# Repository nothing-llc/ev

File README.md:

# nothing-llc/ev

A place for Evan's msr-20-related files.

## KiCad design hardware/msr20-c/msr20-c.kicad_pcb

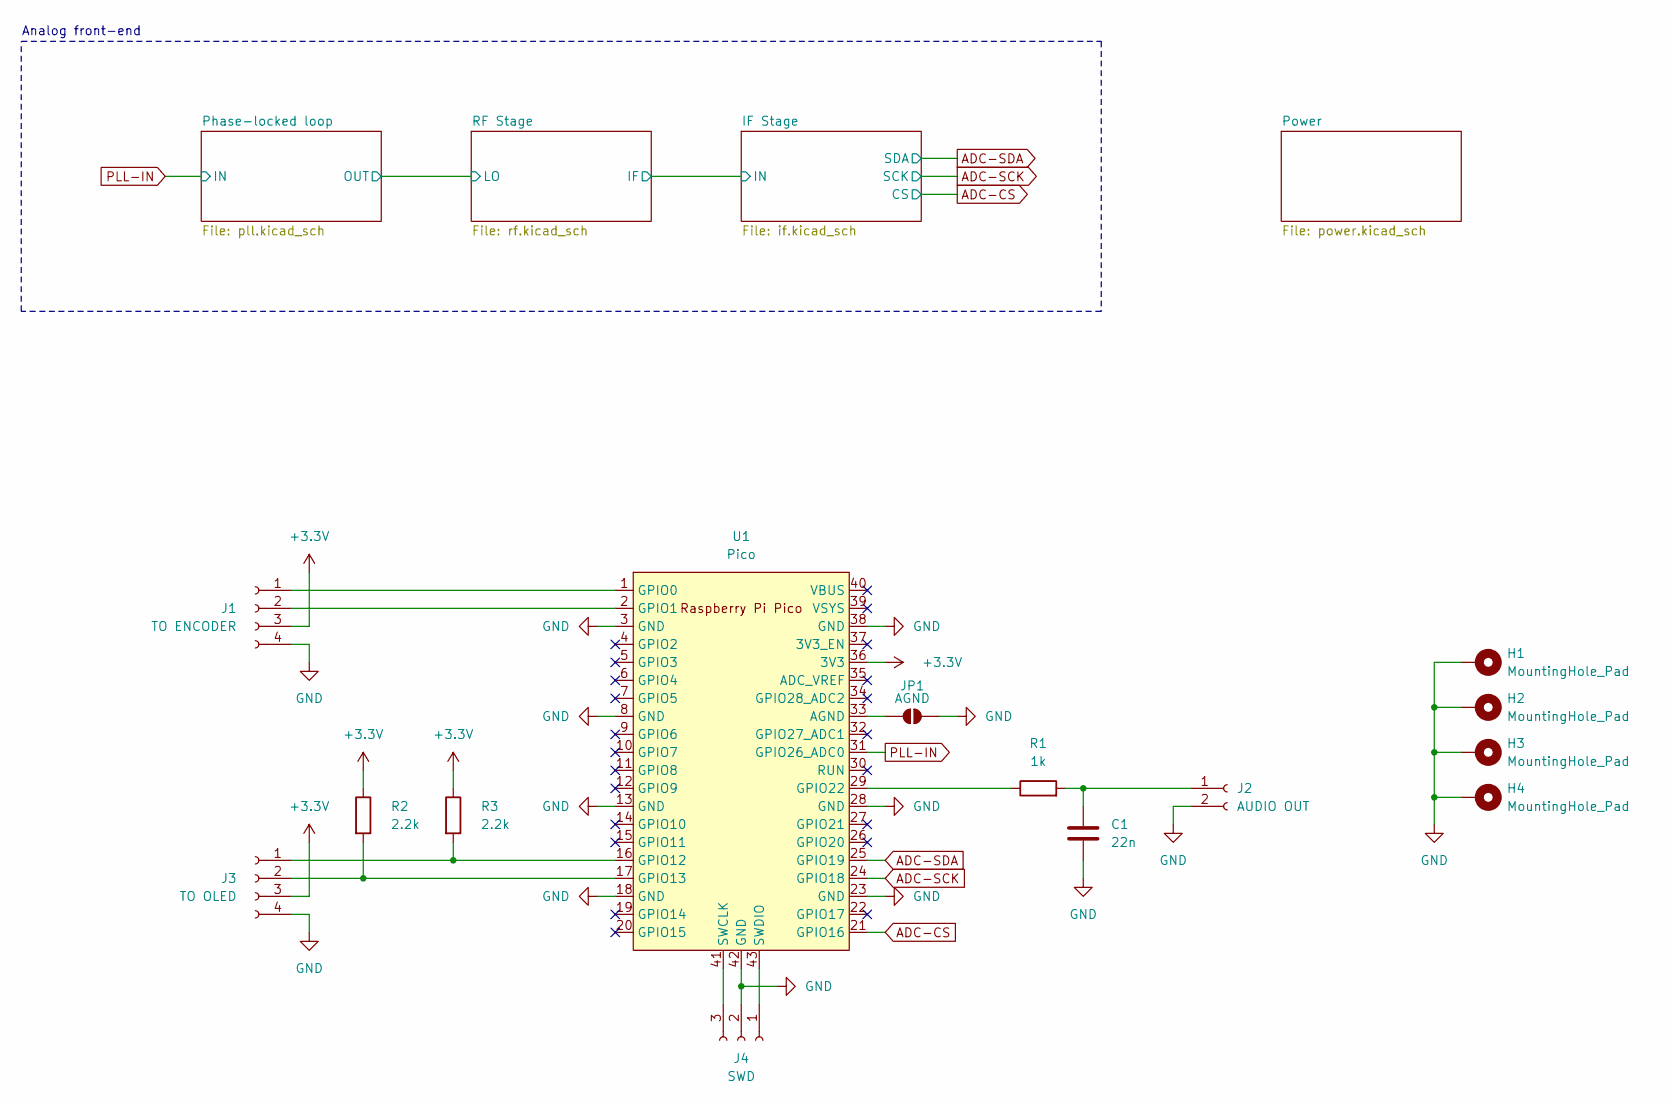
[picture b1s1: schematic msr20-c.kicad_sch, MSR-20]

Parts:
C1: 22n; C_0805_2012Metric
H1, H2, H3, H4: MountingHole_Pad; MountingHole_3.2mm_M3_DIN965_Pad_TopBottom
J1: TO ENCODER; PinHeader_1x04_P2.54mm_Vertical
J2: AUDIO OUT; PinHeader_1x02_P2.54mm_Vertical
J3: TO OLED; PinHeader_1x04_P2.54mm_Vertical
J4: SWD; PinHeader_1x03_P2.54mm_Vertical
JP1: AGND; SolderJumper-2_P1.3mm_Bridged_Pad1.0x1.5mm
R1: 1k; R_0805_2012Metric
R2, R3: 2.2k; R_0805_2012Metric
U1: Pico; RPi_Pico_SMD_TH

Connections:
+3.3V: J1.3, J3.3, R2.1, R3.1, U1.36 (3V3); also elsewhere on the board
ADC-CS: U1.21 (GPIO16); also elsewhere on the board
ADC-SCK: U1.24 (GPIO18); also elsewhere on the board
ADC-SDA: U1.25 (GPIO19); also elsewhere on the board
GND: C1.2, H1.1, H2.1, H3.1, H4.1, J1.4, J2.2, J3.4, J4.2, JP1.2 (B), U1.3 (GND), U1.8 (GND), U1.13 (GND), U1.18 (GND), U1.23 (GND), U1.28 (GND), U1.38 (GND), U1.42 (GND); also elsewhere on the board
unnamed: J1.1, U1.1 (GPIO0)
unnamed: J1.2, U1.2 (GPIO1)
unnamed: C1.1, J2.1, R1.2
unnamed: J3.1, R3.2, U1.16 (GPIO12)
unnamed: J3.2, R2.2, U1.17 (GPIO13)
unnamed: J4.1, U1.43 (SWDIO)
unnamed: J4.3, U1.41 (SWCLK)
unnamed: JP1.1 (A), U1.33 (AGND)
unnamed: R1.1, U1.29 (GPIO22)
PLL-IN: U1.31 (GPIO26_ADC0); also elsewhere on the board

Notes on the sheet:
Analog front-end

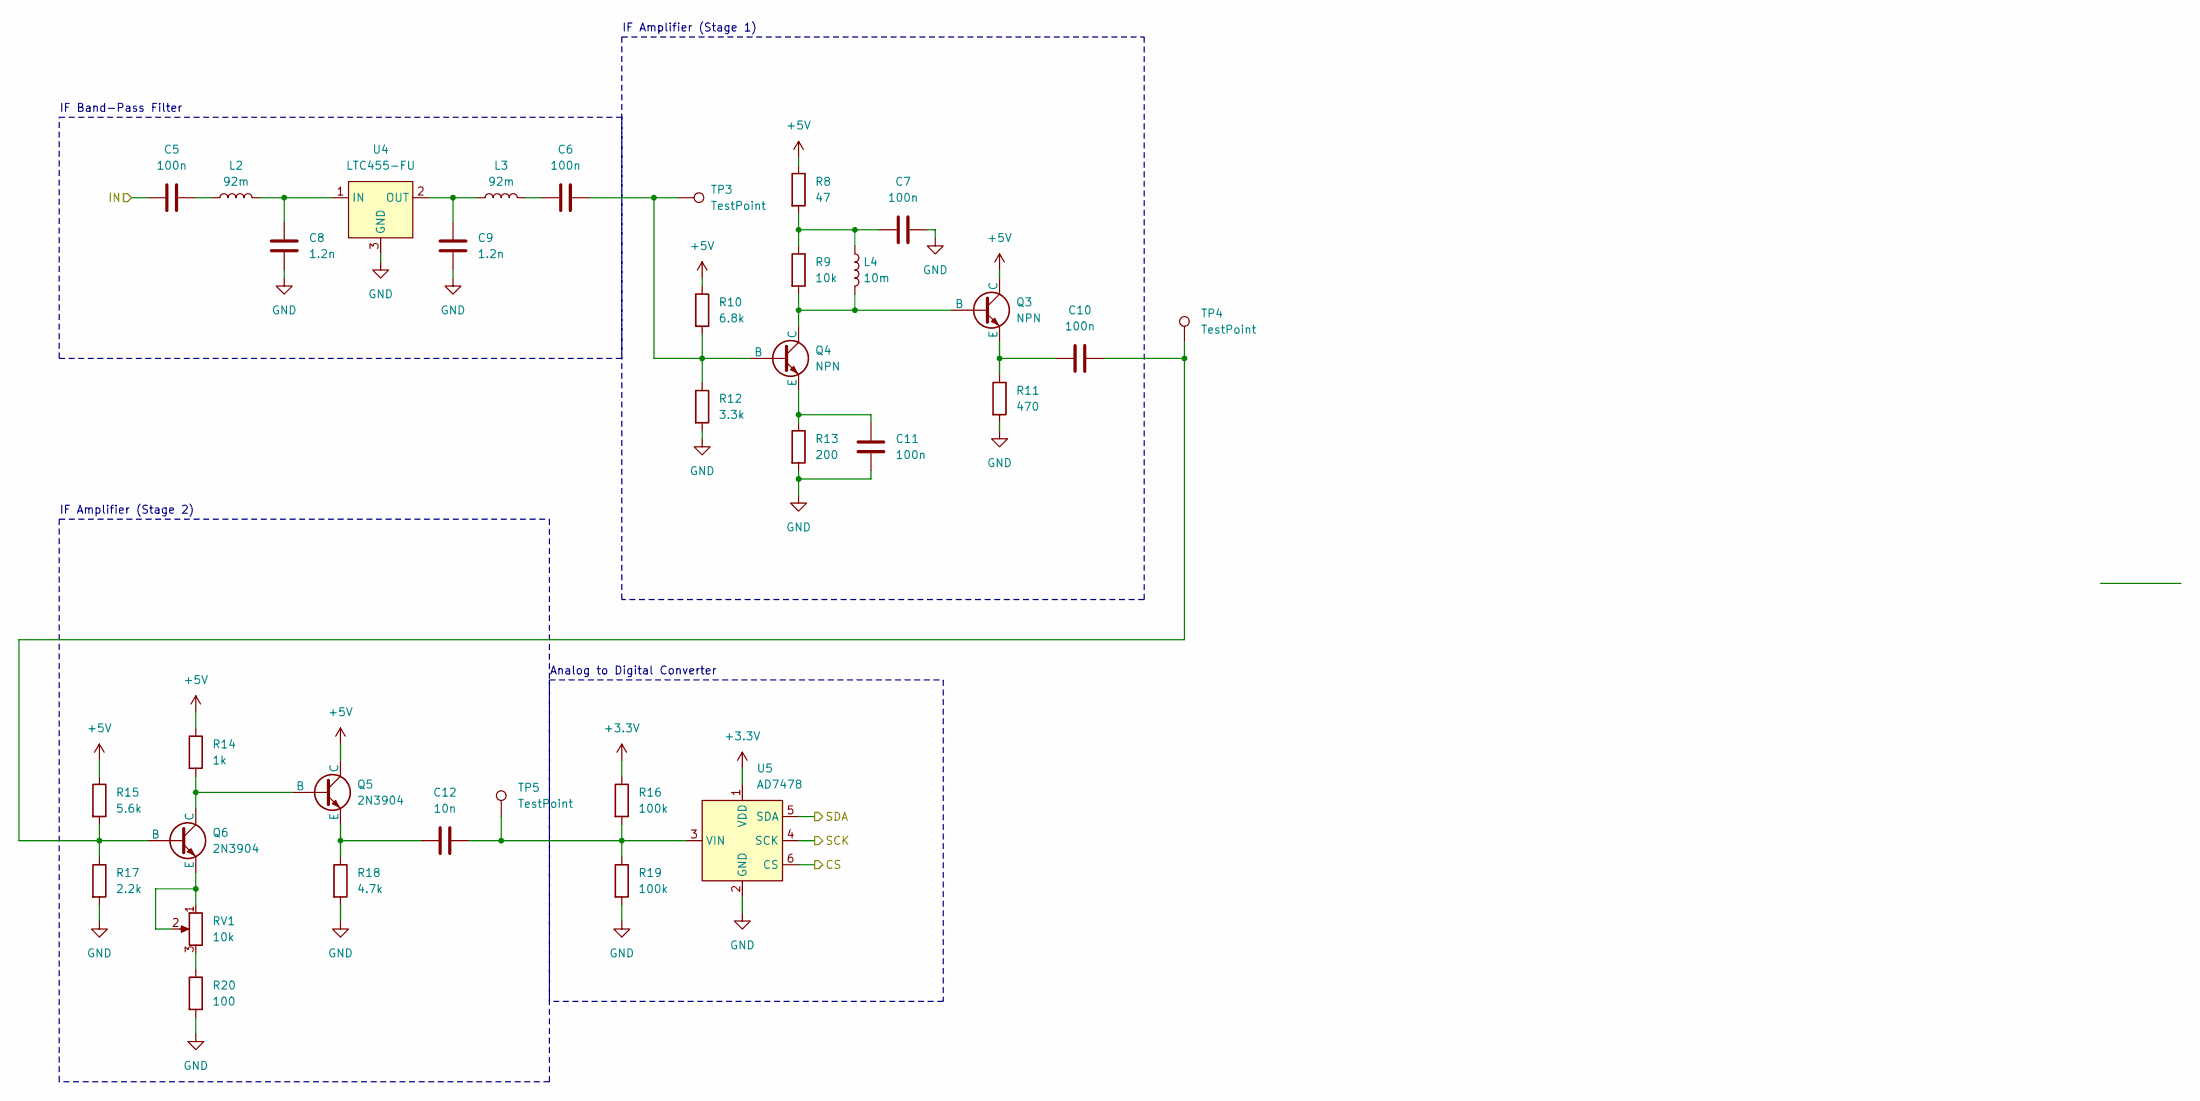
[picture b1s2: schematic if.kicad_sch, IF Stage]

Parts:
C5, C6, C7, C10, C11: 100n; C_0805_2012Metric
C8, C9: 1.2n; C_0805_2012Metric
C12: 10n; C_0805_2012Metric
L2, L3: 92m; L_0805_2012Metric
L4: 10m; L_0805_2012Metric
Q3, Q4: NPN; TO-92
Q5, Q6: 2N3904; TO-92
R8: 47; R_0805_2012Metric
R9: 10k; R_0805_2012Metric
R10: 6.8k; R_0805_2012Metric
R11: 470; R_0805_2012Metric
R12: 3.3k; R_0805_2012Metric
R13: 200; R_0805_2012Metric
R14: 1k; R_0805_2012Metric
R15: 5.6k; R_0805_2012Metric
R16, R19: 100k; R_0805_2012Metric
R17: 2.2k; R_0805_2012Metric
R18: 4.7k; R_0805_2012Metric
R20: 100; R_0805_2012Metric
RV1: 10k; PinHeader_1x03_P2.54mm_Vertical
TP3, TP4, TP5: TestPoint; TestPoint_Pad_D1.0mm
U4: LTC455-FU; LTC455
U5: AD7478; SOT-23-6

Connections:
+3.3V: R16.1, U5.1 (VDD); also elsewhere on the board
+5V: Q3.1 (C), Q5.1 (C), R8.1, R10.1, R14.1, R15.1; also elsewhere on the board
/IF Stage/IN: C5.1; also elsewhere on the board
ADC-CS: U5.6 (CS); also elsewhere on the board
ADC-SCK: U5.4 (SCK); also elsewhere on the board
ADC-SDA: U5.5 (SDA); also elsewhere on the board
GND: C7.2, C8.2, C9.2, C11.1, R11.2, R12.2, R13.2, R17.2, R18.2, R19.2, R20.2, U4.3 (GND), U5.2 (GND); also elsewhere on the board
unnamed: C5.2, L2.1
unnamed: C6.1, L3.2
unnamed: C7.1, L4.1, R8.2, R9.1
unnamed: L4.2, Q3.2 (B), Q4.1 (C), R9.2
unnamed: C10.1, Q3.3 (E), R11.1
unnamed: C6.2, Q4.2 (B), R10.2, R12.1, TP3.1
unnamed: C11.2, Q4.3 (E), R13.1
unnamed: Q5.2 (B), Q6.1 (C), R14.2
unnamed: C12.1, Q5.3 (E), R18.1
unnamed: C10.2, Q6.2 (B), R15.2, R17.1, TP4.1
unnamed: Q6.3 (E), RV1.1, RV1.2
unnamed: R20.1, RV1.3
unnamed: C8.1, L2.2, U4.1 (IN)
unnamed: C9.1, L3.1, U4.2 (OUT)
unnamed: C12.2, R16.2, R19.1, TP5.1, U5.3 (VIN)

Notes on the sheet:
IF Band-Pass Filter
IF Amplifier (Stage 2)
Analog to Digital Converter
IF Amplifier (Stage 1)

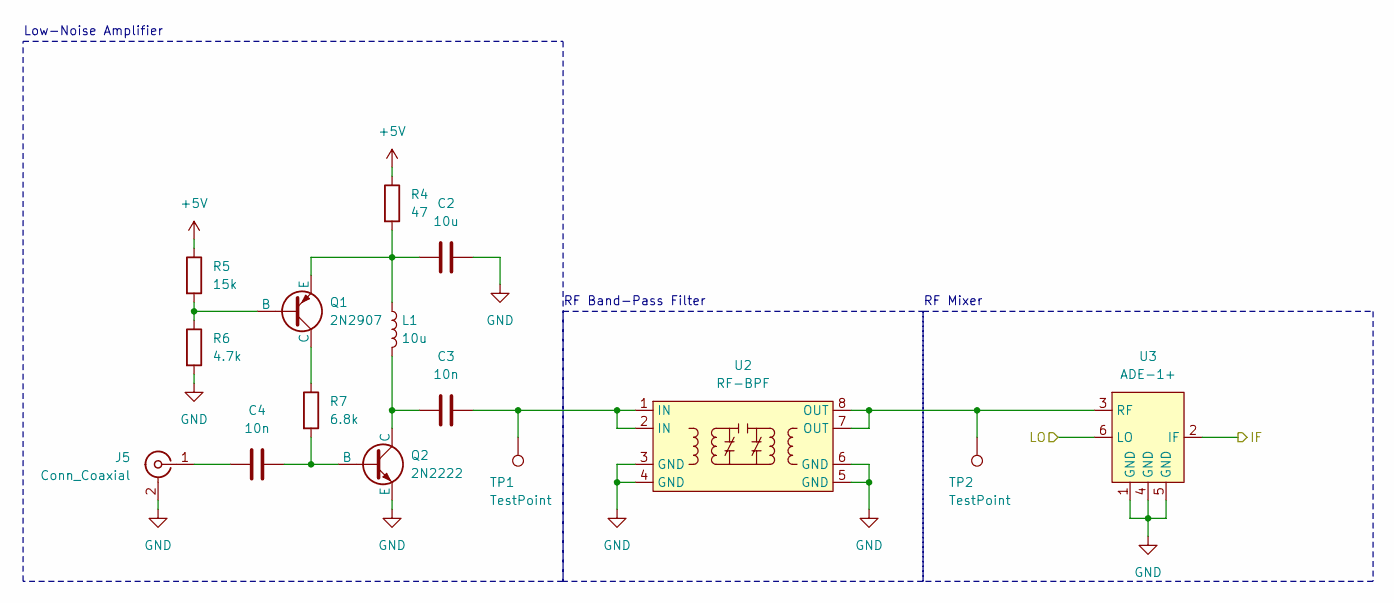
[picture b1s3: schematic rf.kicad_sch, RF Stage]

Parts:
C2: 10u; C_0805_2012Metric
C3, C4: 10n; C_0805_2012Metric
J5: Conn_Coaxial; BNC_TEConnectivity_1478035_Horizontal
L1: 10u; L_0805_2012Metric
Q1: 2N2907; TO-92
Q2: 2N2222; TO-92
R4: 47; R_0805_2012Metric
R5: 15k; R_0805_2012Metric
R6: 4.7k; R_0805_2012Metric
R7: 6.8k; R_0805_2012Metric
TP1, TP2: TestPoint; TestPoint_Pad_D1.0mm
U2: RF-BPF
U3: ADE-1+; Mini-Circuits_CD542_LandPatternPL-052

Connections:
+5V: R4.1, R5.1; also elsewhere on the board
/IF Stage/IN: U3.2 (IF); also elsewhere on the board
/Phase-locked loop/OUT: U3.6 (LO); also elsewhere on the board
GND: C2.2, J5.2 (Ext), Q2.3 (E), R6.2, U2.3 (GND), U2.4 (GND), U2.5 (GND), U2.6 (GND), U3.1 (GND), U3.4 (GND), U3.5 (GND); also elsewhere on the board
unnamed: C3.2, TP1.1, U2.1 (IN), U2.2 (IN)
unnamed: C4.1, J5.1 (In)
unnamed: Q1.2 (B), R5.2, R6.1
unnamed: Q1.1 (C), R7.1
unnamed: C2.1, L1.1, Q1.3 (E), R4.2
unnamed: C4.2, Q2.2 (B), R7.2
unnamed: C3.1, L1.2, Q2.1 (C)
unnamed: TP2.1, U2.7 (OUT), U2.8 (OUT), U3.3 (RF)

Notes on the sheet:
RF Mixer
Low-Noise Amplifier
RF Band-Pass Filter

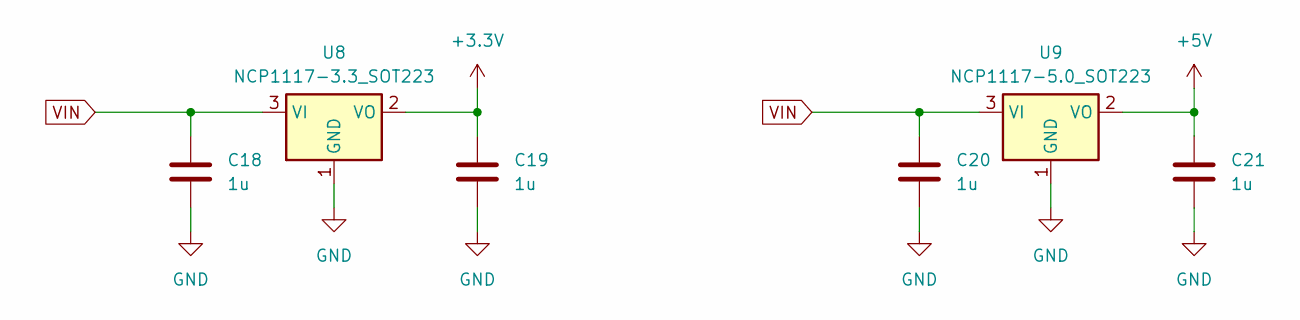
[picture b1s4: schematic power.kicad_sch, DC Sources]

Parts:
C18, C19, C20, C21: 1u; C_0805_2012Metric
U8: NCP1117-3.3_SOT223; SOT-223-3_TabPin2
U9: NCP1117-5.0_SOT223; SOT-223-3_TabPin2

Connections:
+3.3V: C19.1, U8.2 (VO); also elsewhere on the board
+5V: C21.1, U9.2 (VO); also elsewhere on the board
GND: C18.2, C19.2, C20.2, C21.2, U8.1 (GND), U9.1 (GND); also elsewhere on the board
VIN: C18.1, C20.1, U8.3 (VI), U9.3 (VI)

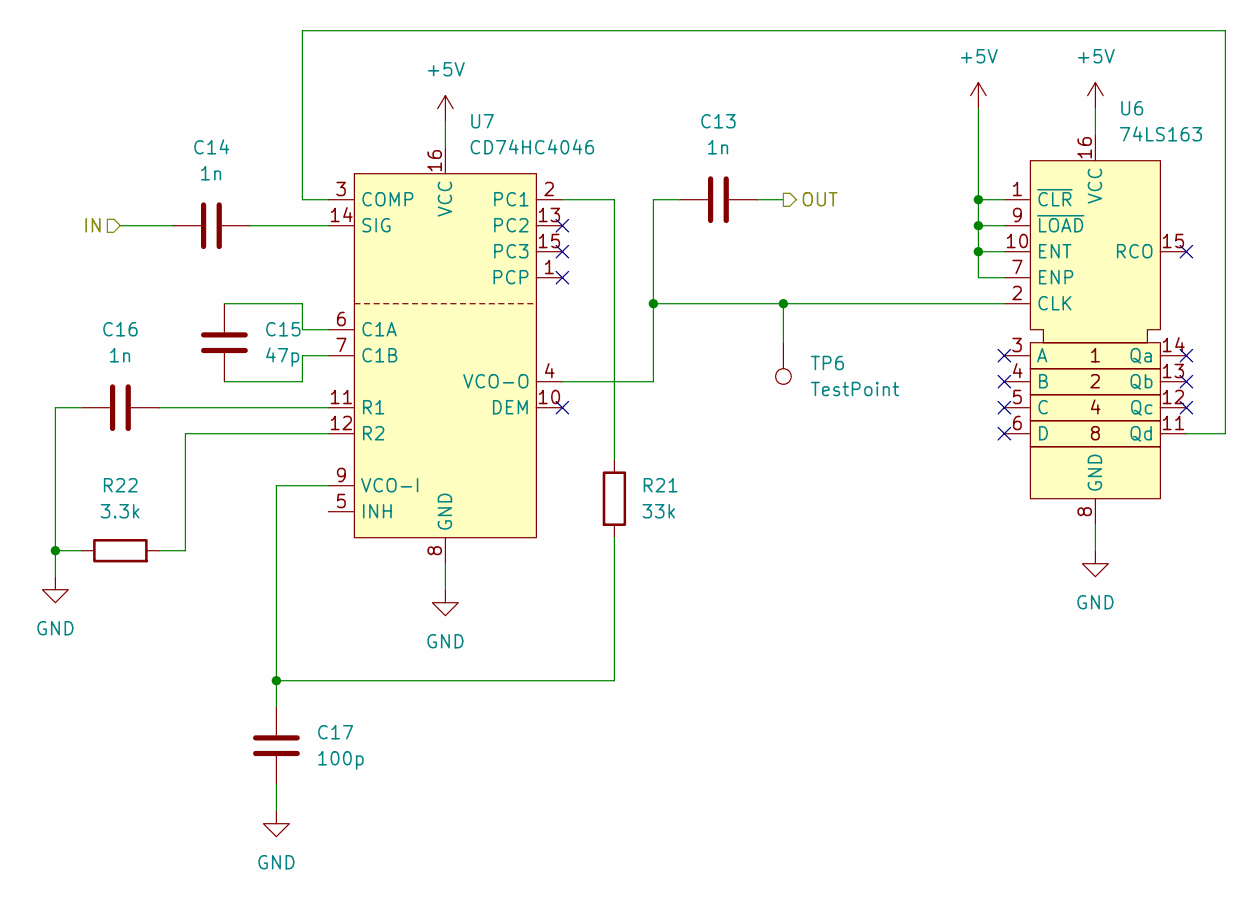
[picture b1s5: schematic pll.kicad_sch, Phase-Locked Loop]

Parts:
C13, C14, C16: 1n; C_0805_2012Metric
C15: 47p; C_0805_2012Metric
C17: 100p; C_0805_2012Metric
R21: 33k; R_0805_2012Metric
R22: 3.3k; R_0805_2012Metric
TP6: TestPoint; TestPoint_Pad_D1.0mm
U6: 74LS163; DIP-16_W7.62mm_LongPads
U7: CD74HC4046; DIP-16_W7.62mm_LongPads

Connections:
+5V: U6.1 (~CLR), U6.7 (ENP), U6.9 (~LOAD), U6.10 (ENT), U6.16 (VCC), U7.16 (VCC); also elsewhere on the board
/Phase-locked loop/OUT: C13.2; also elsewhere on the board
GND: C16.1, C17.1, R22.1, U6.8 (GND), U7.8 (GND); also elsewhere on the board
unnamed: C13.1, TP6.1, U6.2 (CLK), U7.4 (VCO-O)
unnamed: U6.11 (Qd), U7.3 (COMP)
unnamed: C15.2, U7.6 (C1A)
unnamed: C15.1, U7.7 (C1B)
unnamed: R21.1, U7.2 (PC1)
unnamed: C16.2, U7.11 (R1)
unnamed: R22.2, U7.12 (R2)
unnamed: C14.2, U7.14 (SIG)
unnamed: C17.2, R21.2, U7.9 (VCO-I)
PLL-IN: C14.1; also elsewhere on the board

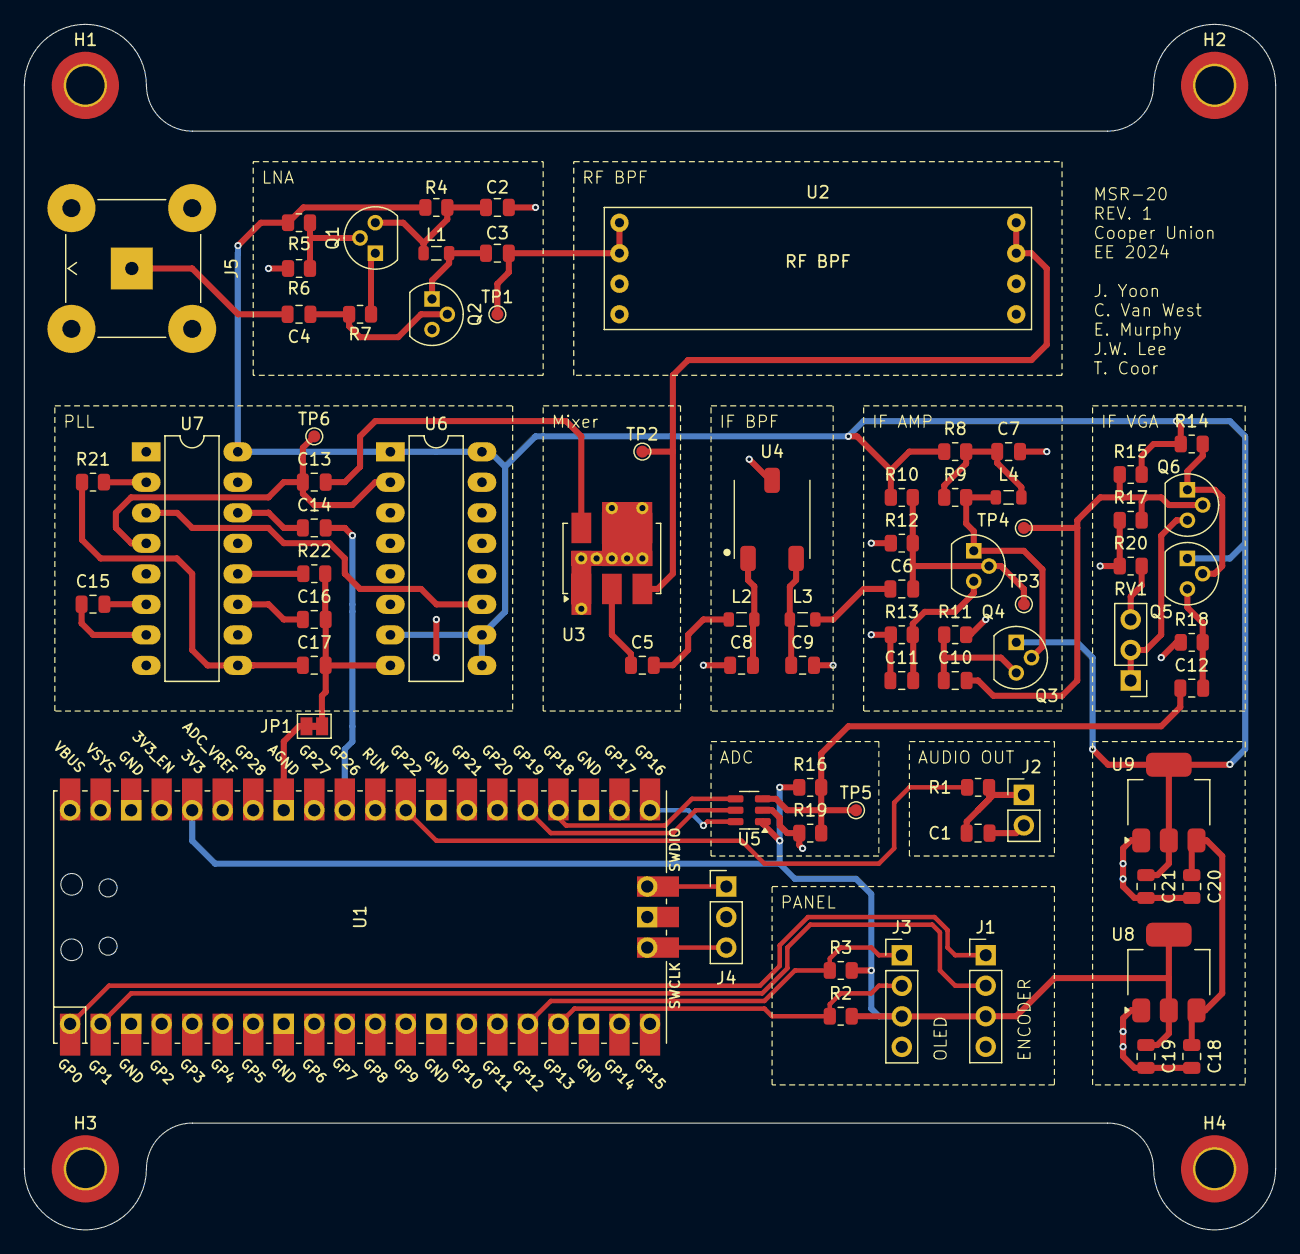
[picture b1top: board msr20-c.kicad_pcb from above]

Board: 2 copper layers, 104.1 x 100.3 mm, 79 parts (0 on the bottom side), 51 nets.

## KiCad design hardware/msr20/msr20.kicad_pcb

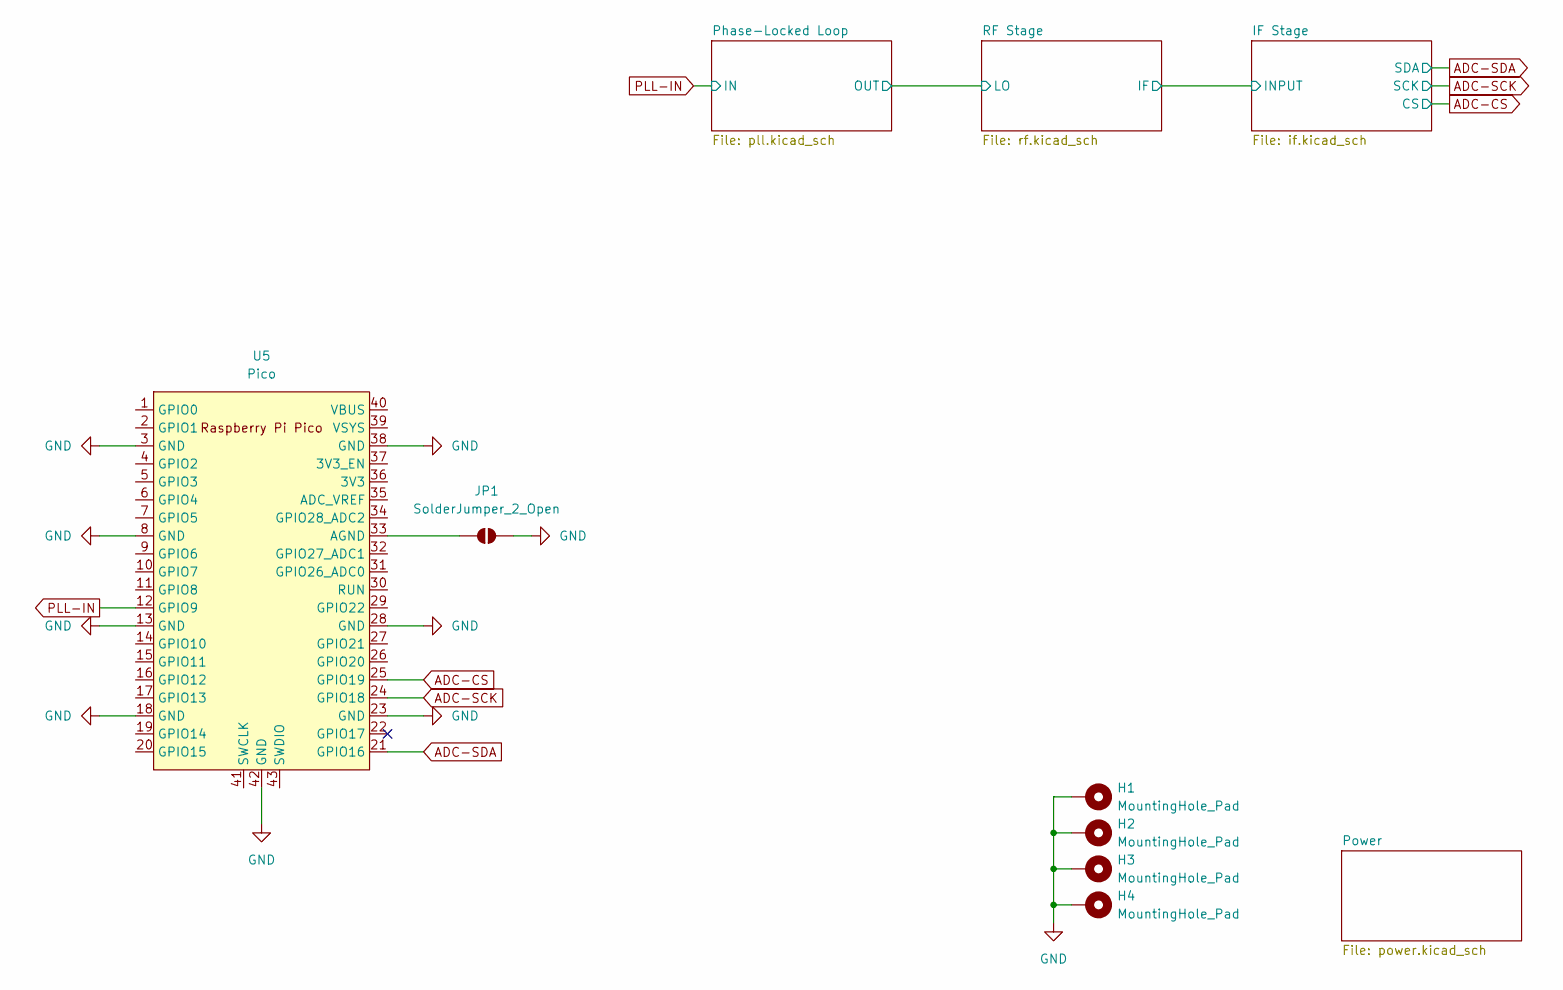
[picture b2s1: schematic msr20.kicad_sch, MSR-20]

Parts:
H1, H2, H3, H4: MountingHole_Pad; MountingHole_3.2mm_M3_DIN965_Pad
JP1: SolderJumper_2_Open; SolderJumper-2_P1.3mm_Bridged2Bar_Pad1.0x1.5mm
U5: Pico; RPi_Pico_SMD_TH

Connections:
ADC-CS: U5.25 (GPIO19); also elsewhere on the board
ADC-SCK: U5.24 (GPIO18); also elsewhere on the board
ADC-SDA: U5.21 (GPIO16); also elsewhere on the board
GND: H1.1, H2.1, H3.1, H4.1, JP1.2 (B), U5.3 (GND), U5.8 (GND), U5.13 (GND), U5.18 (GND), U5.23 (GND), U5.28 (GND), U5.38 (GND), U5.42 (GND); also elsewhere on the board
unnamed: JP1.1 (A), U5.33 (AGND)
PLL-IN: U5.12 (GPIO9); also elsewhere on the board

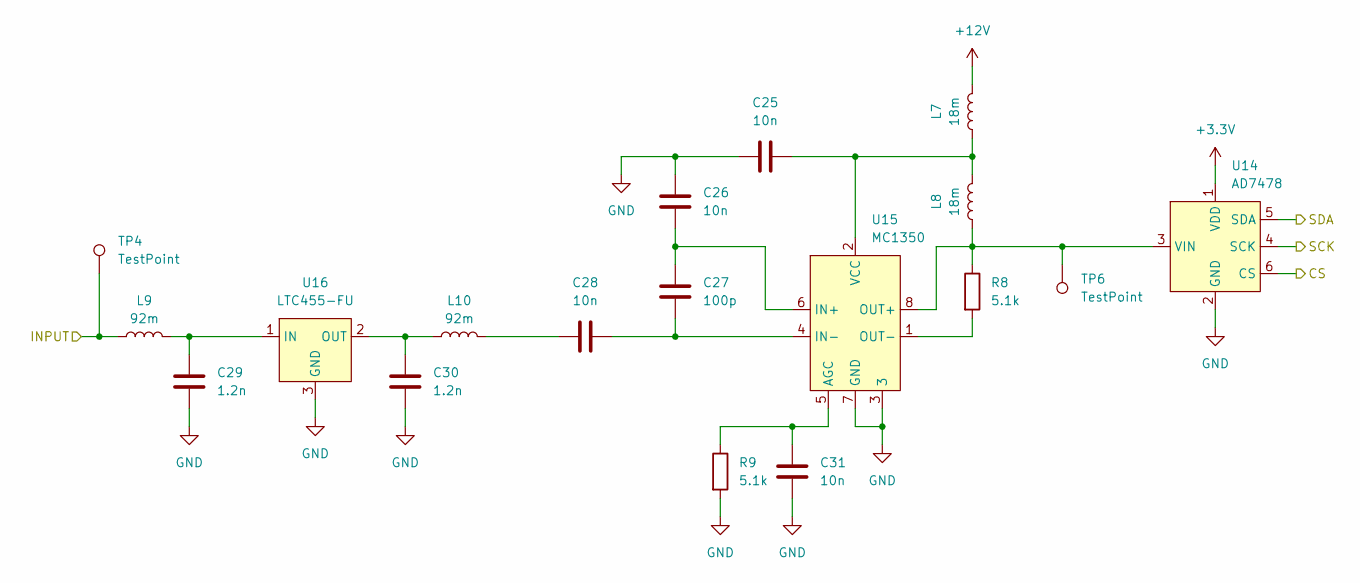
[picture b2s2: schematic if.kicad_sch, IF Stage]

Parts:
C25, C26, C28, C31: 10n; C_0805_2012Metric
C27: 100p; C_0805_2012Metric
C29, C30: 1.2n; C_0805_2012Metric
L7, L8: 18m; L_0805_2012Metric
L9, L10: 92m; L_0805_2012Metric
R8, R9: 5.1k; R_0805_2012Metric
TP4, TP6: TestPoint; TestPoint_Pad_D1.0mm
U14: AD7478; SOT-23-6
U15: MC1350; DIP-8_W7.62mm_LongPads
U16: LTC455-FU; LTC455

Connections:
+3.3V: U14.1 (VDD); also elsewhere on the board
+12V: L7.2; also elsewhere on the board
/IF Stage/INPUT: L9.1, TP4.1; also elsewhere on the board
ADC-CS: U14.6 (CS); also elsewhere on the board
ADC-SCK: U14.4 (SCK); also elsewhere on the board
ADC-SDA: U14.5 (SDA); also elsewhere on the board
GND: C25.1, C26.1, C29.1, C30.1, C31.2, R9.2, U14.2 (GND), U15.3, U15.7 (GND), U16.3 (GND); also elsewhere on the board
unnamed: C28.1, L10.2
unnamed: L8.1, R8.1, TP6.1, U14.3 (VIN), U15.8 (OUT+)
unnamed: C31.1, R9.1, U15.5 (AGC)
unnamed: C26.2, C27.2, U15.6 (IN+)
unnamed: C27.1, C28.2, U15.4 (IN-)
unnamed: R8.2, U15.1 (OUT-)
unnamed: C25.2, L7.1, L8.2, U15.2 (VCC)
unnamed: C29.2, L9.2, U16.1 (IN)
unnamed: C30.2, L10.1, U16.2 (OUT)

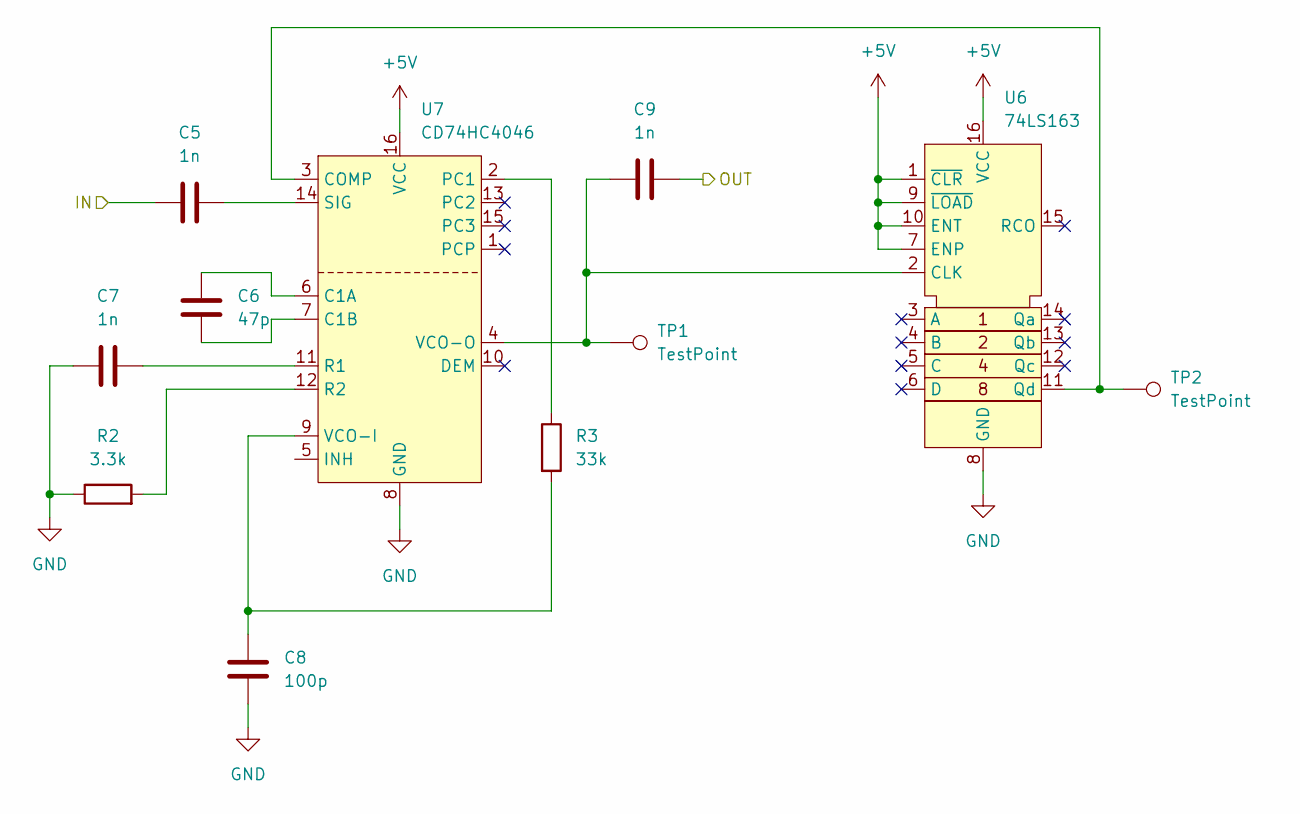
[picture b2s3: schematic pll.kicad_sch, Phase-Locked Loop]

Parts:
C5, C7, C9: 1n; C_0805_2012Metric
C6: 47p; C_0805_2012Metric
C8: 100p; C_0805_2012Metric
R2: 3.3k; R_0805_2012Metric
R3: 33k; R_0805_2012Metric
TP1, TP2: TestPoint; TestPoint_Pad_D1.0mm
U6: 74LS163; DIP-16_W7.62mm_LongPads
U7: CD74HC4046; DIP-16_W7.62mm_LongPads

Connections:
+5V: U6.1 (~CLR), U6.7 (ENP), U6.9 (~LOAD), U6.10 (ENT), U6.16 (VCC), U7.16 (VCC); also elsewhere on the board
/Phase-Locked Loop/OUT: C9.2; also elsewhere on the board
GND: C7.1, C8.1, R2.1, U6.8 (GND), U7.8 (GND); also elsewhere on the board
unnamed: C9.1, TP1.1, U6.2 (CLK), U7.4 (VCO-O)
unnamed: TP2.1, U6.11 (Qd), U7.3 (COMP)
unnamed: C6.2, U7.6 (C1A)
unnamed: C6.1, U7.7 (C1B)
unnamed: R3.1, U7.2 (PC1)
unnamed: C7.2, U7.11 (R1)
unnamed: R2.2, U7.12 (R2)
unnamed: C5.2, U7.14 (SIG)
unnamed: C8.2, R3.2, U7.9 (VCO-I)
PLL-IN: C5.1; also elsewhere on the board

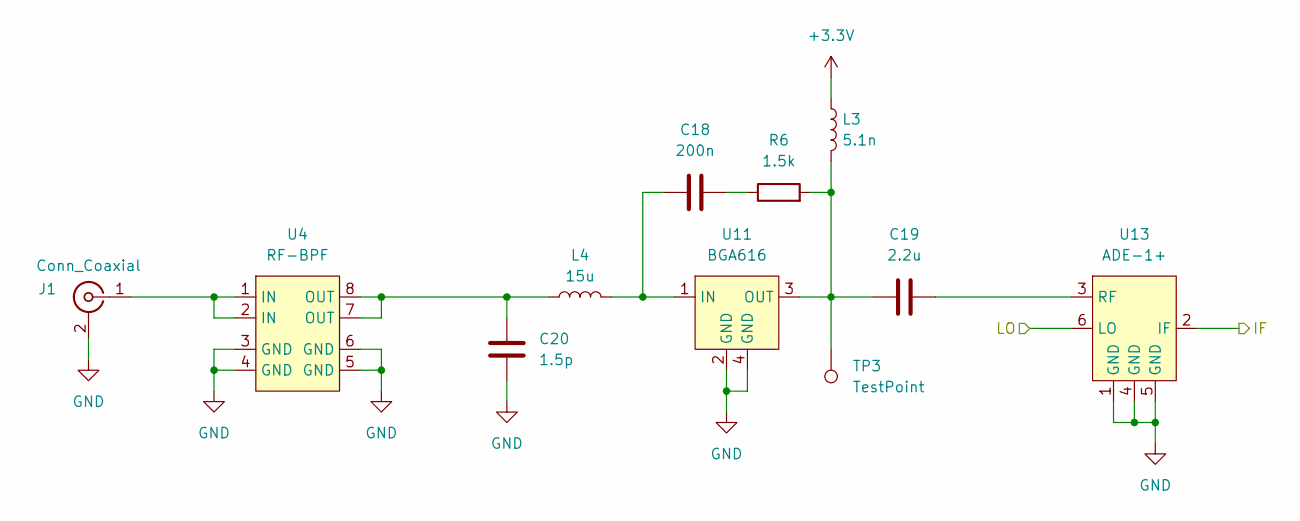
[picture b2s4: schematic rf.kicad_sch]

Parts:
C18: 200n; C_0805_2012Metric
C19: 2.2u; C_0805_2012Metric
C20: 1.5p; C_0805_2012Metric
J1: Conn_Coaxial; BNC_Amphenol_B6252HB-NPP3G-50_Horizontal
L3: 5.1n; L_0805_2012Metric
L4: 15u; L_0805_2012Metric
R6: 1.5k; R_0805_2012Metric
TP3: TestPoint; TestPoint_Pad_D1.0mm
U4: RF-BPF
U11: BGA616
U13: ADE-1+; Mini-Circuits_CD636_H4.11mm

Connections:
+3.3V: L3.1; also elsewhere on the board
/IF Stage/INPUT: U13.2 (IF); also elsewhere on the board
/Phase-Locked Loop/OUT: U13.6 (LO); also elsewhere on the board
GND: C20.2, J1.2 (Ext), U4.3 (GND), U4.4 (GND), U4.5 (GND), U4.6 (GND), U11.2 (GND), U11.4 (GND), U13.1 (GND), U13.4 (GND), U13.5 (GND); also elsewhere on the board
unnamed: C18.2, R6.1
unnamed: C20.1, L4.1, U4.7 (OUT), U4.8 (OUT)
unnamed: J1.1 (In), U4.1 (IN), U4.2 (IN)
unnamed: C18.1, L4.2, U11.1 (IN)
unnamed: C19.1, L3.2, R6.2, TP3.1, U11.3 (OUT)
unnamed: C19.2, U13.3 (RF)

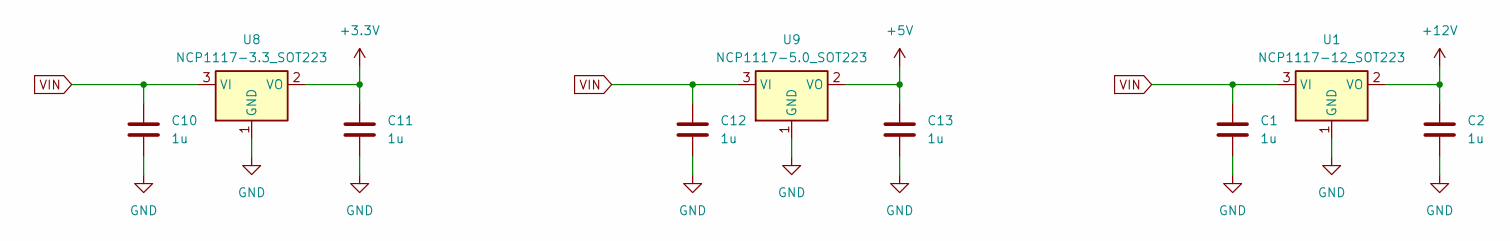
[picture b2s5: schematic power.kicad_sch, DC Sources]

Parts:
C1, C2, C10, C11, C12, C13: 1u; C_0805_2012Metric
U1: NCP1117-12_SOT223; SOT-223-3_TabPin2
U8: NCP1117-3.3_SOT223; SOT-223-3_TabPin2
U9: NCP1117-5.0_SOT223; SOT-223-3_TabPin2

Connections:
+3.3V: C11.1, U8.2 (VO); also elsewhere on the board
+5V: C13.1, U9.2 (VO); also elsewhere on the board
+12V: C2.1, U1.2 (VO); also elsewhere on the board
GND: C1.2, C2.2, C10.2, C11.2, C12.2, C13.2, U1.1 (GND), U8.1 (GND), U9.1 (GND); also elsewhere on the board
VIN: C1.1, C10.1, C12.1, U1.3 (VI), U8.3 (VI), U9.3 (VI)

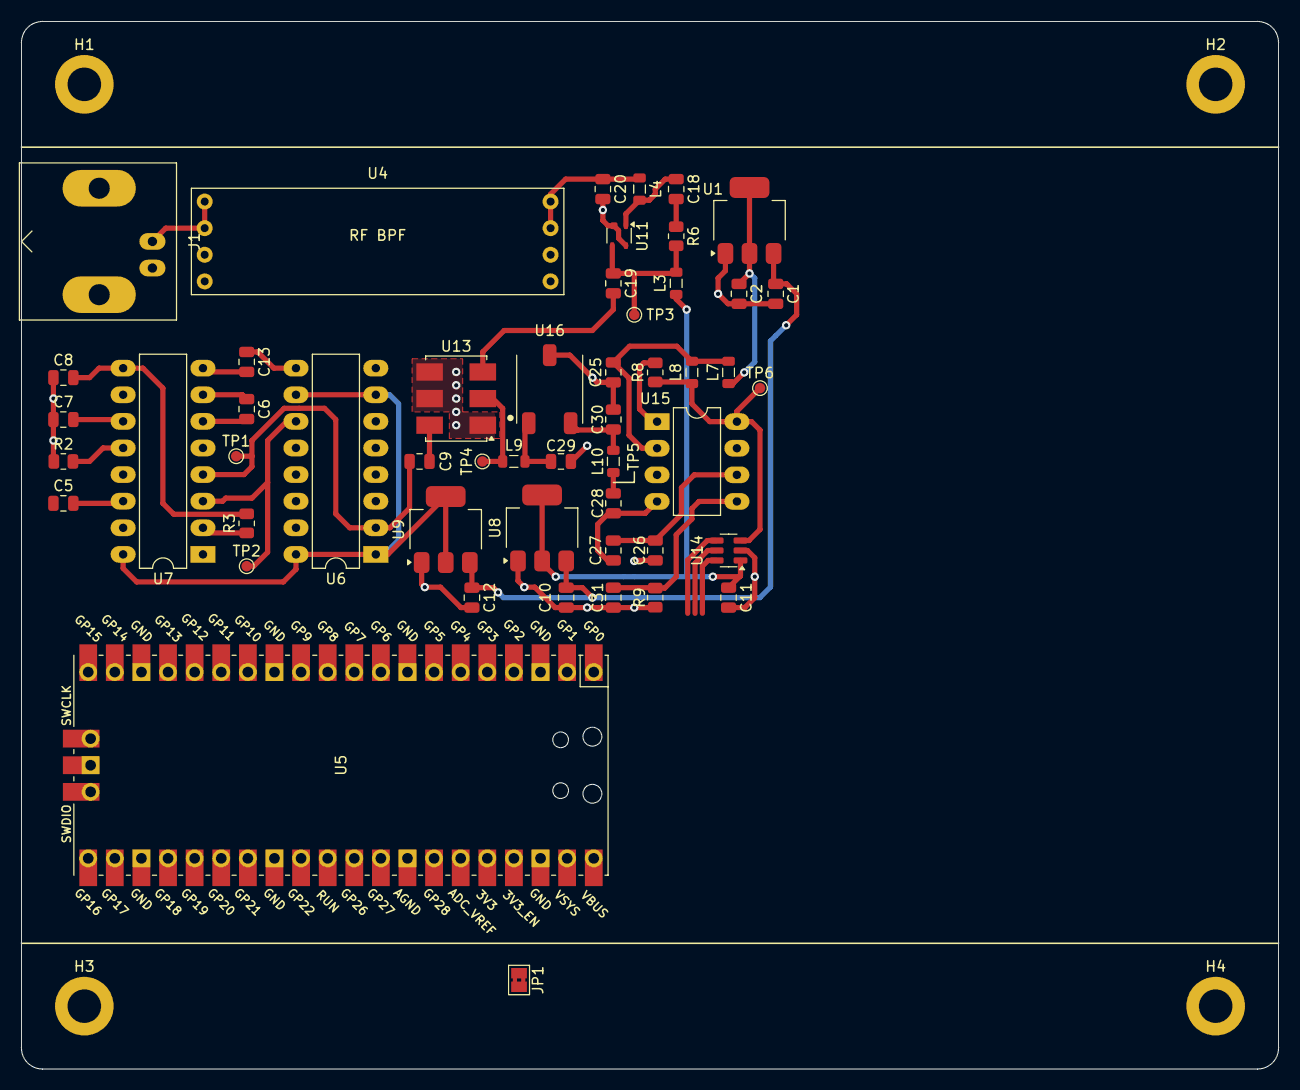
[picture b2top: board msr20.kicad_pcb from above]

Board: 2 copper layers, 120.0 x 100.0 mm, 55 parts (0 on the bottom side), 36 nets.

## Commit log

2024-03-26 create kicad project with symbol and footprint libraries
2024-03-26 add link to pcb to-do list
2024-03-27 add ade-1+ symbol
2024-03-27 add bga616, ltc455-fu symbols
2024-03-28 add rf-bpf symbol
2024-03-28 add ad7478 symbol
2024-03-28 add pico symbol and footprint
2024-03-28 misc
2024-03-28 update bga616 symbol pins
2024-03-28 add cd74hc4046 symbol
2024-03-28 create mc1350 symbol
2024-03-28 add adc and pico to sch
2024-03-28 add sn74ls163 symbol, update symbol datasheets, descriptions
2024-03-28 Add pll schematic
2024-03-28 save
2024-03-29 create ltc455 symbol
2024-03-29 create rf-bpf footprint
2024-03-29 create pcb file, add enclosure dimensions
2024-03-29 assign footprints for active components
2024-04-02 add power sheet to schematic, add 3.3v, 5v regulators to schematic
2024-04-02 initial board layout; dimensions
2024-04-03 update footprint assignments for passives
2024-04-03 rf-bpf, lna, pll, rf mixer added to pcb
2024-04-14 add if filter and if amplifier to schematic, organize into sheet hierarchy
2024-04-14 assign footprints to passives in if stage
2024-04-14 add 12v regulator
2024-04-14 add if section to pcb
2024-04-15 add test points to schematic
2024-04-15 ground routing
2024-04-15 power and ground routing
2024-04-20 add lna schematic and new rf-bpf symbol
2024-04-20 draft of rf stage
2024-04-20 add pll to schematic
2024-04-20 add bpf and fixed-gain amp to if stage
2024-04-23 add stage 2 amp and adc to if schematic
2024-04-23 add pico to schematic
2024-04-23 add swd connector to schematic
2024-04-23 add audio out and lpf to sch
2024-04-28 add power sheet, assign footprints
2024-04-29 pcb: pll, lna, rf-bpf layout
2024-04-29 finish pcb rev 1, new png render
2024-04-29 plot msr20-c schematic and pcb
